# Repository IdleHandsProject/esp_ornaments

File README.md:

# esp_ornaments
The best way to spread Christmas cheer is to upload it to the internet!
New version soon!

Buy the high current boards here:

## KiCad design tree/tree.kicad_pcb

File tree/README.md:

# youtubeplaybutton
An Arduino YouTube Play Button

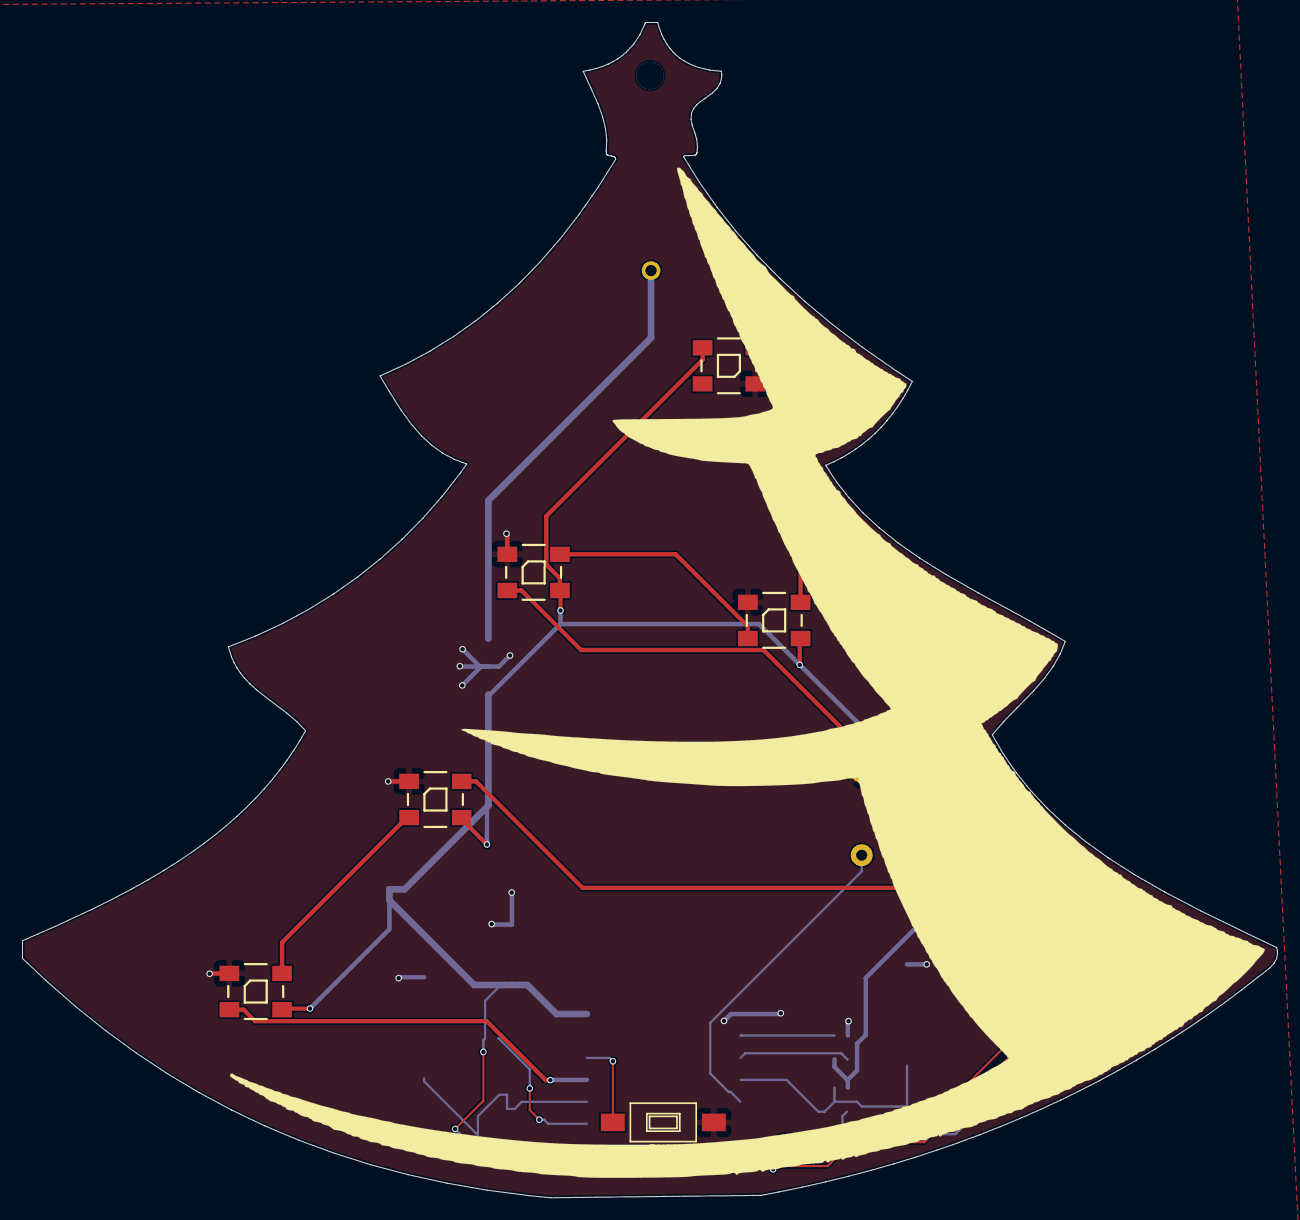
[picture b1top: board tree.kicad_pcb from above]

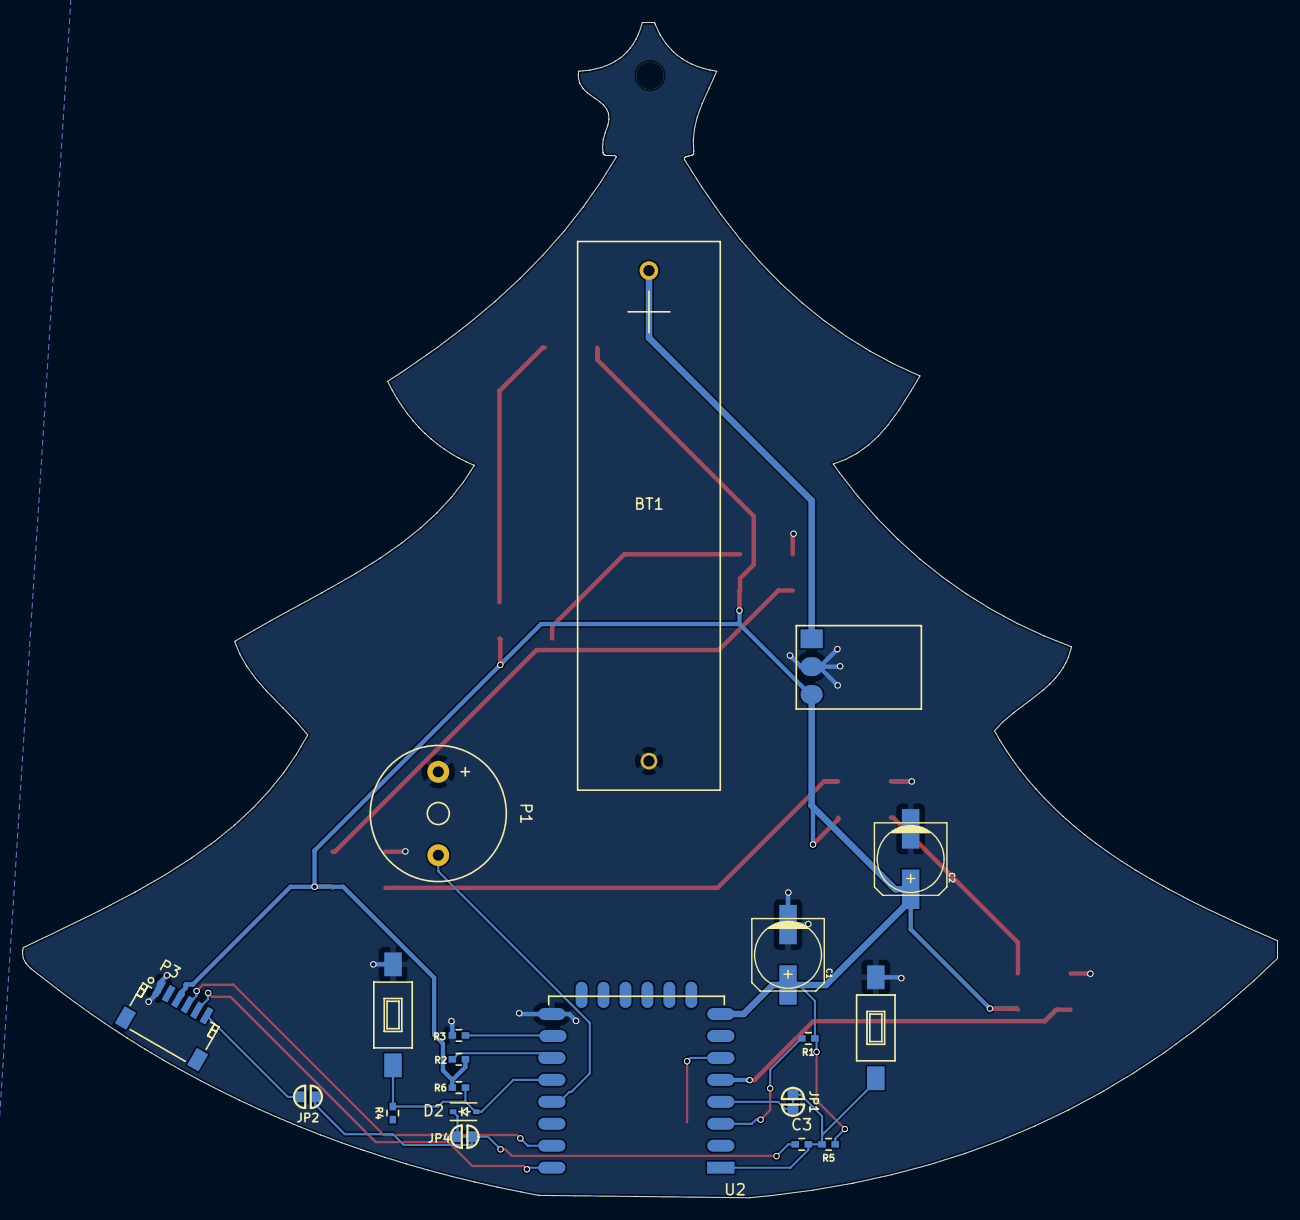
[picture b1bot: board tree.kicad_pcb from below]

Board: 2 copper layers, 114.4 x 107.1 mm, 27 parts (20 on the bottom side), 20 nets.

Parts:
BT1: Batt_N; AAA_SingleHolder
C1, C2: 100uF; c_elec_6.3x5.3
C3: 1uF; C_0402_Hand
D2: D; SOD-323
JP1: Jumper_NC_Small; SOLDER-JUMPER_1-WAY-CLOSED
JP2: Jumper_NO_Small; SOLDER-JUMPER_1-WAY
JP4: Jumper_NC_Small; SOLDER-JUMPER_1-WAY
LED1, LED2, LED3, LED4, LED5, LED6: WS2812B
P1: CONN_01X02; Buzzer_12x9.5RM7.6
P2: EXT_REG; pololu_power_3.3v-5v
P3: CONN_01X06; Connectors_JST_SM06B-SRSS-TB
R1, R2, R5: 10K; R_0402_Hand
R3, R4, R6: 1K; R_0402_Hand
SW1: B; SW_SPST_FSMSM
SW2: GPIO0; SW_SPST_FSMSM
SW3: RESET; SW_SPST_FSMSM
U2: ESP-12E; ESP-12E_NoTH

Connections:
+3V3: C1.1, C2.1, LED1.1, LED2.1, LED3.1, LED4.1, LED5.1, LED6.1, P2.3, P3.3, R1.1, R2.1, R5.1, R6.1, U2.8
/BUTT1: SW1.2, U2.6
/CH_PD: R1.2, U2.3
/GPIO0: D2.2, R4.2, R6.2, SW2.2, U2.18
/GPIO2: R2.2, U2.17
/GPIO15: R3.1, U2.16
/GPIO16: C3.2, JP1.1, JP1.2, R5.2, SW3.2, U2.1, U2.4
/NEOP: LED1.4, U2.5
/RXD: P3.4, U2.21
/TXD: P3.5, U2.22
/VIN: BT1.1, P2.1
/tonepin: P1.2, U2.19
DTR: C3.1, D2.1, JP2.2, JP4.1, JP4.2
GND: BT1.2, C1.2, C2.2, LED1.3, LED2.3, LED3.3, LED4.3, LED5.3, LED6.3, P1.1, P2.2, P3.1, R3.2, SW1.1, SW2.1, SW3.1, U2.15
unnamed: JP2.1, P3.6
unnamed: LED1.2, LED2.4
unnamed: LED2.2, LED3.4
unnamed: LED3.2, LED4.4
unnamed: LED4.2, LED5.4
unnamed: LED5.2, LED6.4

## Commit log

2016-12-20 First Commit! Its a mess
2016-12-20 Added Firmware
2016-12-20 Firmware Update
2016-12-20 Firmware Fix
2017-01-01 Remove extra README's
